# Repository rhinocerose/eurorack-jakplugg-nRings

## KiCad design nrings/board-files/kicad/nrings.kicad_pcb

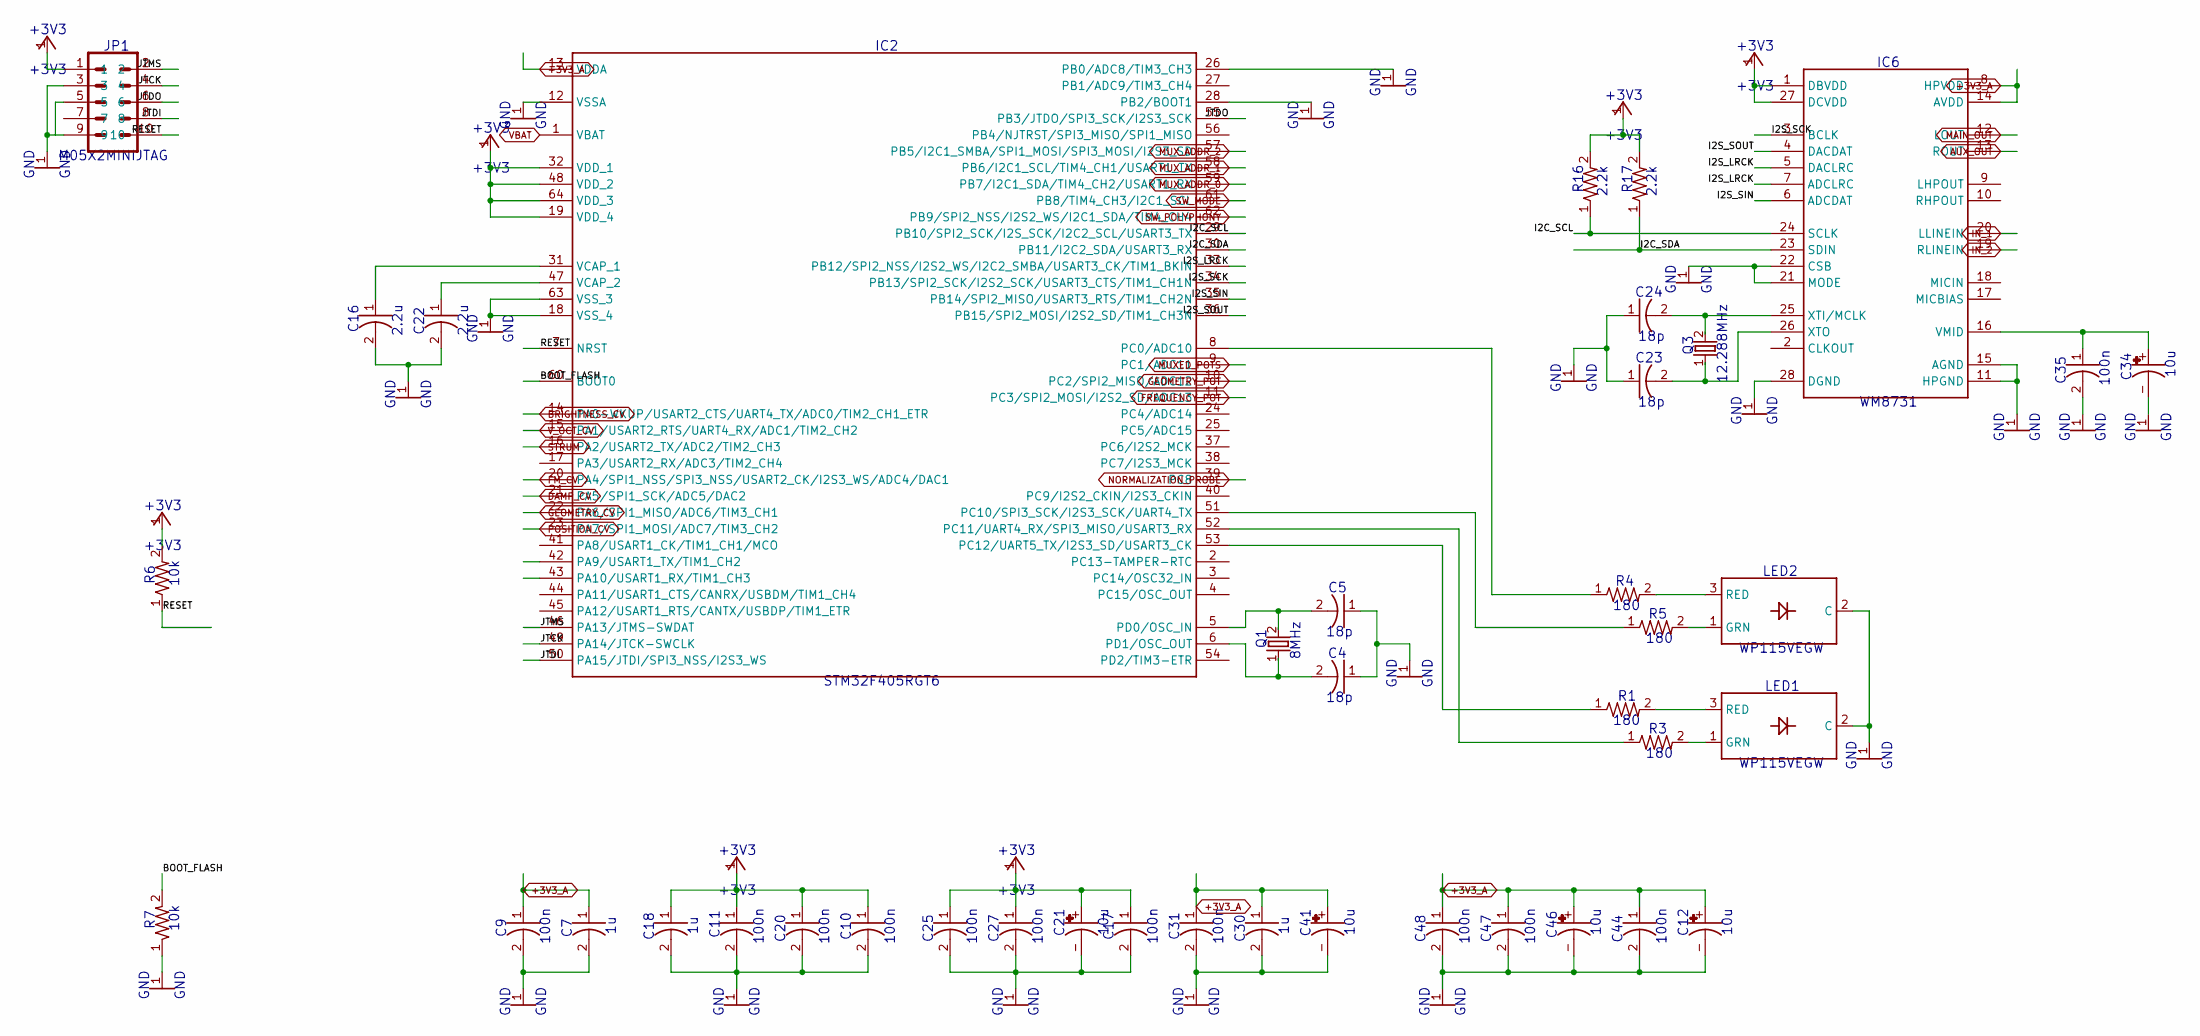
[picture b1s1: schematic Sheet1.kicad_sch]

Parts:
C4, C5, C23, C24: 18p; CAP_0603
C7, C18, C30: 1u; CAP_0603
C9, C10, C11, C17, C20, C25, C27, C31, C35, C44, C47, C48: 100n; CAP_0603
C12, C21, C34, C41, C46: 10u; PANASONIC_A
C16, C22: 2.2u; CAP_0805
IC2: STM32F405RGT6; TQFP-10X10-64
IC6: WM8731; SSOP28
JP1: M05X2MINIJTAG; 2X5-1.27
LED1, LED2: WP115VEGW; LED-BICOLOR-THROUGHHOLE
Q1: 8MHz; TSC_7A_CRYSTAL
Q3: 12.288MHz; TSC_7A_CRYSTAL
R1, R3, R4, R5: 180; RES_0603
R6, R7: 10k; RES_0603
R16, R17: 2.2k; RES_0603

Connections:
+3V3: C10.1, C11.1, C17.1, C18.1, C20.1, C21.+, C25.1, C27.1, IC2.19 (VDD_4), IC2.32 (VDD_1), IC2.48 (VDD_2), IC2.64 (VDD_3), IC6.1 (DBVDD), IC6.27 (DCVDD), JP1.1, R6.2, R16.2, R17.2; also elsewhere on the board
+3V3_A: C7.1, C9.1, C12.+, C30.1, C31.1, C41.+, C44.1, C46.+, C47.1, C48.1, IC2.13 (VDDA), IC6.8 (HPVDD), IC6.14 (AVDD); also elsewhere on the board
AUX_OUT: IC6.13 (ROUT); also elsewhere on the board
BOOT_FLASH: IC2.60 (BOOT0), R7.2
BRIGHTNESS_CV: IC2.14 (PA0-WKUP/USART2_CTS/UART4_TX/ADC0/TIM2_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); also elsewhere on the board
DAMP_CV: IC2.21 (PA5/SPI1_SCK/ADC5/DAC2); also elsewhere on the board
FM_CV: IC2.20 (PA4/SPI1_NSS/SPI3_NSS/USART2_CK/I2S3_WS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); also elsewhere on the board
FREQUENCY_POT: IC2.11 (PC3/SPI2_MOSI/I2S2_SD/ADC13); also elsewhere on the board
GEOMETRY_CV: IC2.22 (PA6/SPI1_MISO/ADC6/TIM3_CH1); also elsewhere on the board
GEOMETRY_POT: IC2.10 (PC2/SPI2_MISO/ADC12); also elsewhere on the board
GND: C4.1, C5.1, C7.2, C9.2, C10.2, C11.2, C12.-, C16.2, C17.2, C18.2, C20.2, C21.-, C22.2, C23.1, C24.1, C25.2, C27.2, C30.2, C31.2, C34.-, C35.2, C41.-, C44.2, C46.-, C47.2, C48.2, IC2.12 (VSSA), IC2.18 (VSS_4), IC2.26 (PB0/ADC8/TIM3_CH3), IC2.28 (PB2/BOOT1), IC2.63 (VSS_3), IC6.11 (HPGND), IC6.15 (AGND), IC6.21 (MODE), IC6.22 (CSB), IC6.28 (DGND), JP1.3, JP1.5, JP1.9, LED1.2 (C), LED2.2 (C), R7.1; also elsewhere on the board
I2C_SCL: IC2.29 (PB10/SPI2_SCK/I2S_SCK/I2C2_SCL/USART3_TX), IC6.24 (SCLK), R16.1
I2C_SDA: IC2.30 (PB11/I2C2_SDA/USART3_RX), IC6.23 (SDIN), R17.1
I2S_LRCK: IC2.33 (PB12/SPI2_NSS/I2S2_WS/I2C2_SMBA/USART3_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), IC6.5 (DACLRC), IC6.7 (ADCLRC)
I2S_SCK: IC2.34 (PB13/SPI2_SCK/I2S2_SCK/USART3_CTS/TIM1_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), IC6.3 (BCLK)
I2S_SIN: IC2.35 (PB14/SPI2_MISO/USART3_RTS/TIM1_CH2N), IC6.6 (ADCDAT)
I2S_SOUT: IC2.36 (PB15/SPI2_MOSI/I2S2_SD/TIM1_CH3N), IC6.4 (DACDAT)
IN_1: IC6.20 (LLINEIN); also elsewhere on the board
IN_2: IC6.19 (RLINEIN); also elsewhere on the board
JTCK: IC2.49 (PA14/JTCK-SWCLK), JP1.4
JTDI: IC2.50 (PA15/JTDI/SPI3_NSS/I2S3_WS), JP1.8
JTDO: IC2.55 (PB3/JTDO/SPI3_SCK/I2S3_SCK), JP1.6
JTMS: IC2.46 (PA13/JTMS-SWDAT), JP1.2
MAIN_OUT: IC6.12 (LOUT); also elsewhere on the board
MUXED_POTS: IC2.9 (PC1/ADC11); also elsewhere on the board
MUX_ADDR_0: IC2.59 (PB7/I2C1_SDA/TIM4_CH2/USART1_RX); also elsewhere on the board
MUX_ADDR_1: IC2.58 (PB6/I2C1_SCL/TIM4_CH1/USART1_TX); also elsewhere on the board
MUX_ADDR_2: IC2.57 (PB5/I2C1_SMBA/SPI1_MOSI/SPI3_MOSI/I2S3_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); also elsewhere on the board
unnamed: C5.2, IC2.5 (PD0/OSC_IN), Q1.2
unnamed: C4.2, IC2.6 (PD1/OSC_OUT), Q1.1
unnamed: LED1.3 (RED), R1.2
unnamed: C22.1, IC2.47 (VCAP_2)
unnamed: C34.+, C35.1, IC6.16 (VMID)
unnamed: C16.1, IC2.31 (VCAP_1)
unnamed: LED1.1 (GRN), R3.2
unnamed: LED2.3 (RED), R4.2
unnamed: LED2.1 (GRN), R5.2
unnamed: IC2.52 (PC11/UART4_RX/SPI3_MISO/USART3_RX), R3.1
unnamed: IC2.8 (PC0/ADC10), R4.1
unnamed: C24.2, IC6.25 (XTI/MCLK), Q3.2
unnamed: C23.2, IC6.26 (XTO), Q3.1
unnamed: IC2.53 (PC12/UART5_TX/I2S3_SD/USART3_CK), R1.1
unnamed: IC2.51 (PC10/SPI3_SCK/I2S3_SCK/UART4_TX), R5.1
NORMALIZATION_PROBE: IC2.39 (PC8); also elsewhere on the board
POSITION_CV: IC2.23 (PA7/SPI1_MOSI/ADC7/TIM3_CH2); also elsewhere on the board
RESET: IC2.7 (NRST), JP1.10, R6.1
STRUM: IC2.16 (PA2/USART2_TX/ADC2/TIM2_CH3); also elsewhere on the board
SW_MODE: IC2.61 (PB8/TIM4_CH3/I2C1_SCL); also elsewhere on the board
SW_POLYPHONY: IC2.62 (PB9/SPI2_NSS/I2S2_WS/I2C1_SDA/TIM4_CH4); also elsewhere on the board
V_OCT_CV: IC2.15 (PA1/USART2_RTS/UART4_RX/ADC1/TIM2_CH2); also elsewhere on the board

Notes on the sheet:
10u
C21
GND
180
C20
WM8731
C27
C16
C46
STM32F405RGT6
C18
C10
C31
C41
10k
WP115VEGW
C23
C22
LED2
+3V3
100n
8MHz
18p
IC2
M05X2MINIJTAG
JP1
2.2k
IC6
C48
R16
C11
R17
LED1
C12
C17
C47
C25
C44
C24
C30

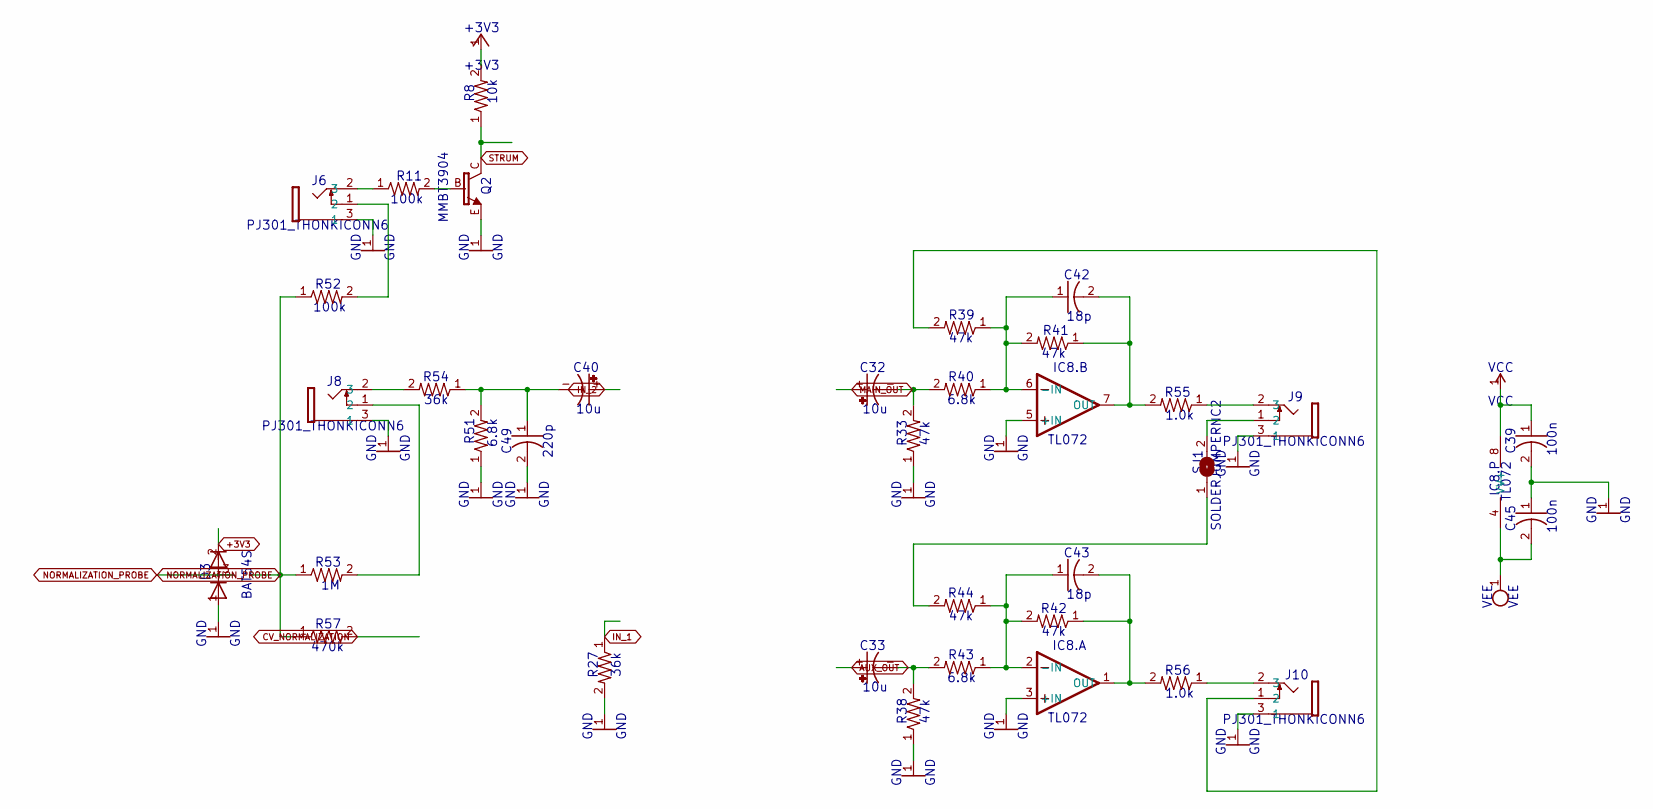
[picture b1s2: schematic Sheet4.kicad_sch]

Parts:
C32, C33, C40: 10u; PANASONIC_A
C39, C45: 100n; CAP_0603
C42, C43: 18p; CAP_0603
C49: 220p; CAP_0603
D3: BAT54S; SOT23
IC8: TL072; SO08
J6, J8, J9, J10: PJ301_THONKICONN6; THONKICONN
Q2: MMBT3904; SOT23-BEC
R8: 10k; RES_0603
R11, R52: 100k; RES_0603
R27, R54: 36k; RES_0603
R33, R38, R39, R41, R42, R44: 47k; RES_0603
R40, R43, R51: 6.8k; RES_0603
R53: 1M; RES_0603
R55, R56: 1.0k; RES_0603
R57: 470k; RES_0603
SJ1: SOLDERJUMPERNC2; SJ_2S-NOTRACE

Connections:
+3V3: D3.2 (C), R8.2; also elsewhere on the board
AUX_OUT: C33.+; also elsewhere on the board
CV_NORMALIZATION: R57.2; also elsewhere on the board
GND: C39.2, C45.1, C49.2, D3.1 (A), IC8.3 (+IN), IC8.5 (+IN), J6.3 (1), J8.3 (1), J9.3 (1), J10.3 (1), Q2.E, R27.2, R33.1, R38.1, R51.1; also elsewhere on the board
IN_1: R27.1; also elsewhere on the board
IN_2: C40.+; also elsewhere on the board
MAIN_OUT: C32.+; also elsewhere on the board
unnamed: J6.2 (3), R11.1
unnamed: C40.-, C49.1, R51.2, R54.1
unnamed: J6.1 (2), R52.2
unnamed: J8.2 (3), R54.2
unnamed: C33.-, R38.2, R43.2
unnamed: C43.1, IC8.2 (-IN), R42.2, R43.1, R44.1
unnamed: C43.2, IC8.1 (OUT), R42.1, R56.2
unnamed: J10.2 (3), R56.1
unnamed: C32.-, R33.2, R40.2
unnamed: C42.1, IC8.6 (-IN), R39.1, R40.1, R41.2
unnamed: C42.2, IC8.7 (OUT), R41.1, R55.2
unnamed: J9.2 (3), R55.1
unnamed: J8.1 (2), R53.2
unnamed: J10.1 (2), R39.2
unnamed: R44.2, SJ1.1
unnamed: J9.1 (2), SJ1.2
unnamed: Q2.B, R11.2
NORMALIZATION_PROBE: D3.3 (AC), R52.1, R53.1, R57.1; also elsewhere on the board
STRUM: Q2.C, R8.1; also elsewhere on the board
VCC: C39.1, IC8.8 (V+); also elsewhere on the board
VEE: C45.2, IC8.4 (V-); also elsewhere on the board

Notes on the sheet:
GND
1.0k
220p
6.8k
C49
R55
47k
10k
R56
R39
C42
100k
36k
R11
C40
SOLDERJUMPERNC2
R38
470k
SJ1
C33
PJ301_THONKICONN6
+3V3
R54
R40
10u
VEE
R57
R43
R51
R52
MMBT3904
J10
100n
C32
C43
R33
IC8.P
TL072
VCC
18p

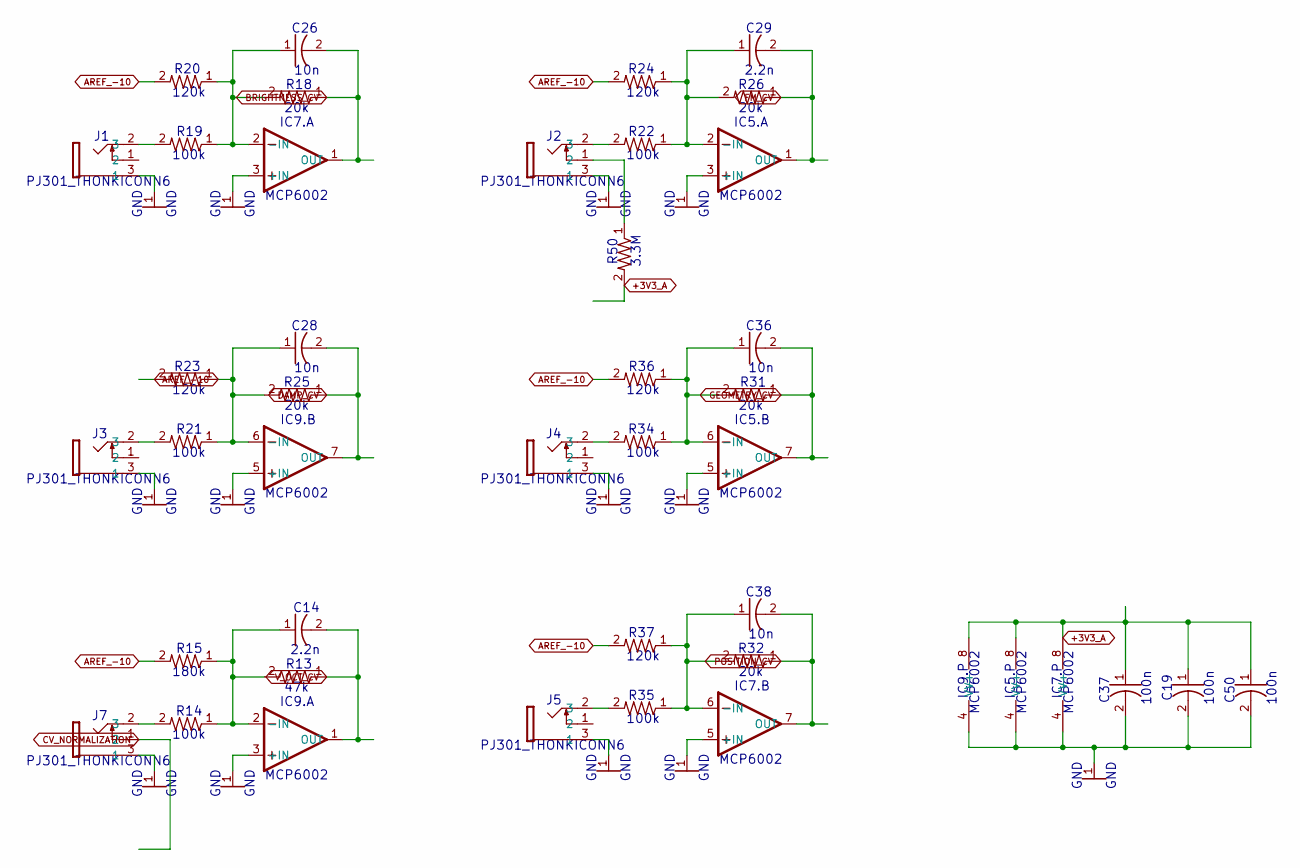
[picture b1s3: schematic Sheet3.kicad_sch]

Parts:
C14, C29: 2.2n; CAP_0603
C19, C37, C50: 100n; CAP_0603
C26, C28, C36, C38: 10n; CAP_0603
IC5, IC7, IC9: MCP6002; SO08
J1, J2, J3, J4, J5, J7: PJ301_THONKICONN6; THONKICONN
R13: 47k; RES_0603
R14, R19, R21, R22, R34, R35: 100k; RES_0603
R15: 180k; RES_0603
R18, R25, R26, R31, R32: 20k; RES_0603
R20, R23, R24, R36, R37: 120k; RES_0603
R50: 3.3M; RES_0603

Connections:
+3V3_A: C19.1, C37.1, C50.1, IC5.8 (V+), IC7.8 (V+), IC9.8 (V+), R50.2; also elsewhere on the board
AREF_-10: R15.2, R20.2, R23.2, R24.2, R36.2, R37.2; also elsewhere on the board
BRIGHTNESS_CV: C26.2, IC7.1 (OUT), R18.1; also elsewhere on the board
CV_NORMALIZATION: J7.1 (2); also elsewhere on the board
DAMP_CV: C28.2, IC9.7 (OUT), R25.1; also elsewhere on the board
FM_CV: C29.2, IC5.1 (OUT), R26.1; also elsewhere on the board
GEOMETRY_CV: C36.2, IC5.7 (OUT), R31.1; also elsewhere on the board
GND: C19.2, C37.2, C50.2, IC5.3 (+IN), IC5.4 (V-), IC5.5 (+IN), IC7.3 (+IN), IC7.4 (V-), IC7.5 (+IN), IC9.3 (+IN), IC9.4 (V-), IC9.5 (+IN), J1.3 (1), J2.3 (1), J3.3 (1), J4.3 (1), J5.3 (1), J7.3 (1); also elsewhere on the board
unnamed: J1.2 (3), R19.2
unnamed: C26.1, IC7.2 (-IN), R18.2, R19.1, R20.1
unnamed: J7.2 (3), R14.2
unnamed: J2.2 (3), R22.2
unnamed: C29.1, IC5.2 (-IN), R22.1, R24.1, R26.2
unnamed: J4.2 (3), R34.2
unnamed: J3.2 (3), R21.2
unnamed: C28.1, IC9.6 (-IN), R21.1, R23.1, R25.2
unnamed: C14.1, IC9.2 (-IN), R13.2, R14.1, R15.1
unnamed: C36.1, IC5.6 (-IN), R31.2, R34.1, R36.1
unnamed: J5.2 (3), R35.2
unnamed: C38.1, IC7.6 (-IN), R32.2, R35.1, R37.1
unnamed: J2.1 (2), R50.1
POSITION_CV: C38.2, IC7.7 (OUT), R32.1; also elsewhere on the board
V_OCT_CV: C14.2, IC9.1 (OUT), R13.1; also elsewhere on the board

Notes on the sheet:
R31
10n
20k
MCP6002
IC9.B
GND
PJ301_THONKICONN6
2.2n
C50
R20
IC7.P
100k
C26
C29
3.3M
R50
C28
R24
100n
47k
C19
120k
IC7.B
IC5.P
R18
R14
C14
R25
R26
R19
C37
R15
IC9.A
IC5.A
R37
R21
IC9.P
R22
R35
R32

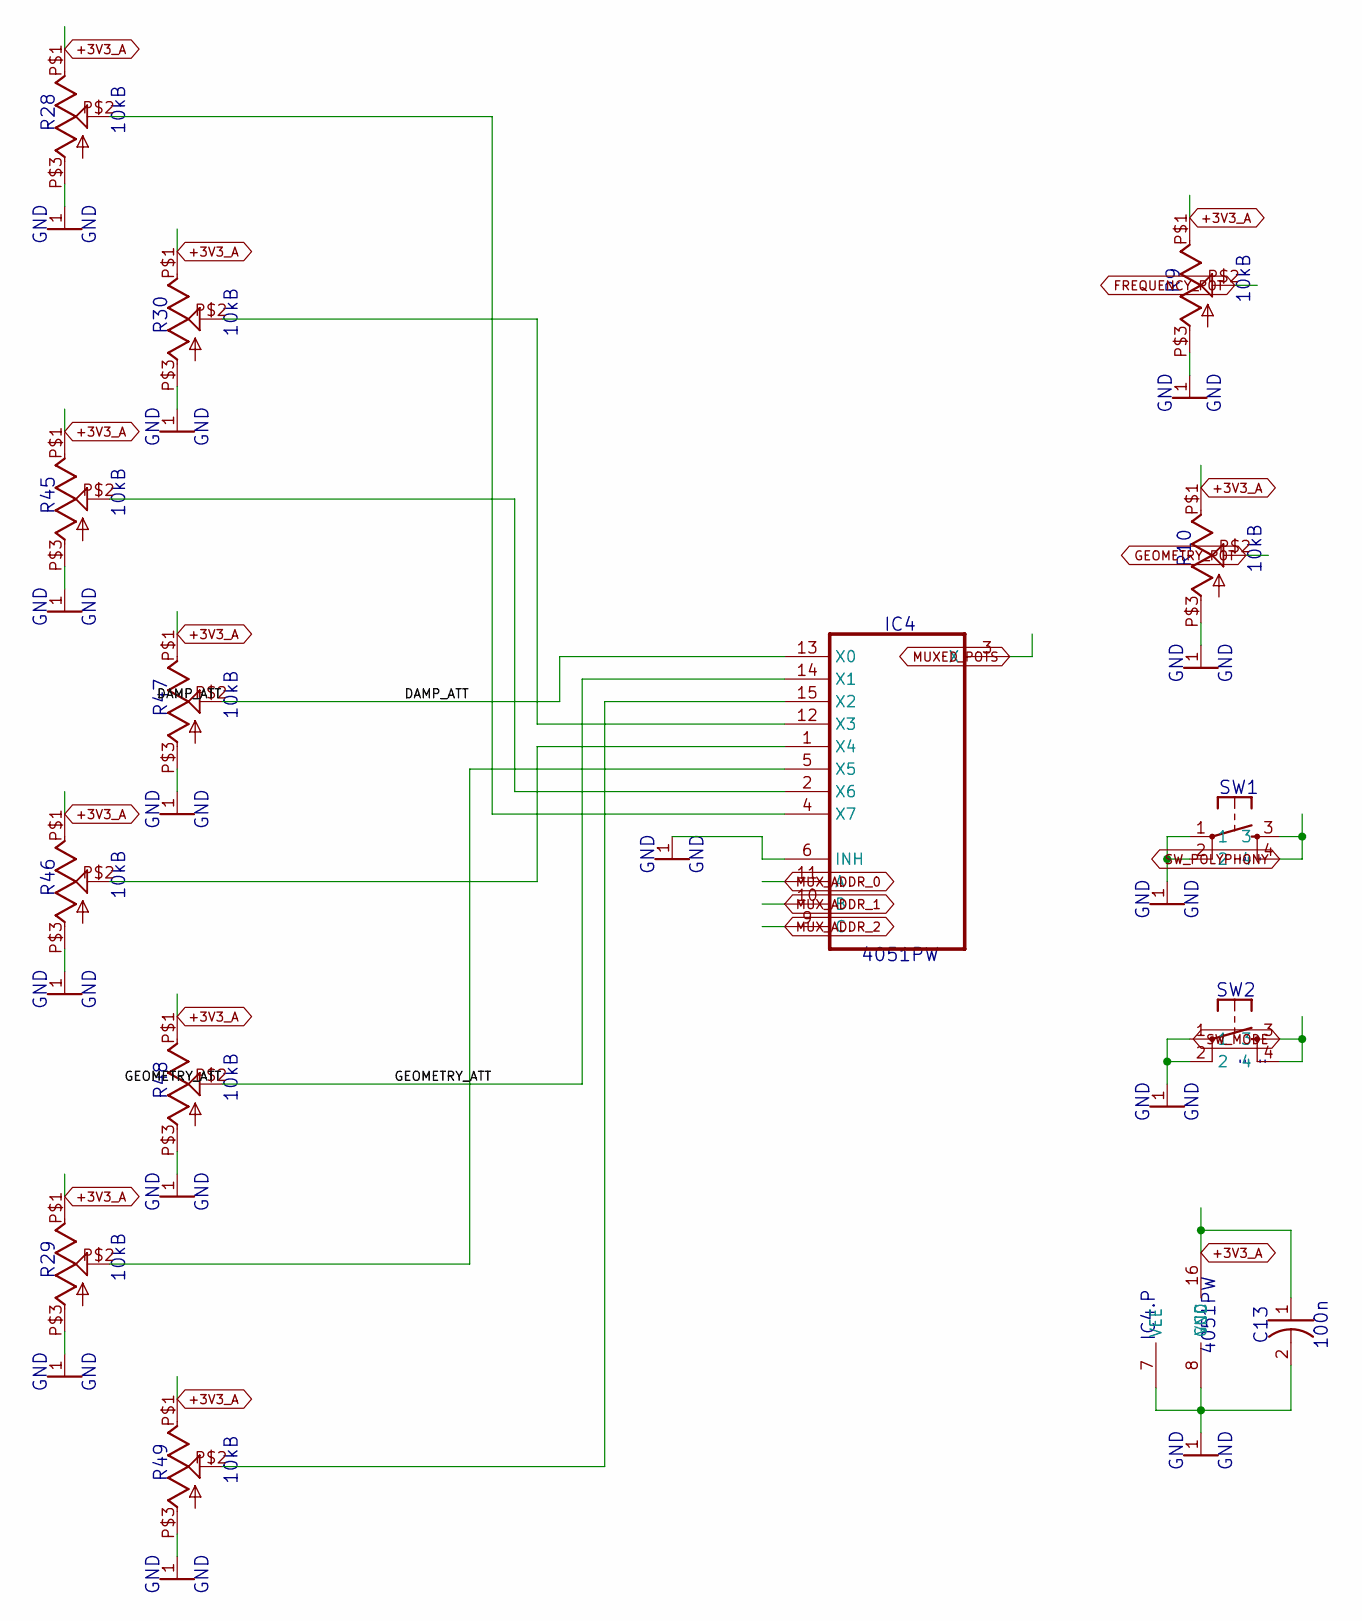
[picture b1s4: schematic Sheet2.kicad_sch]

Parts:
C13: 100n; CAP_0603
IC4: 4051PW; TSSOP16
R9, R10, R28, R29, R30: 10kB; ALPS_POT_VERTICAL_PS
R45, R46, R47, R48, R49: 10kB; ALPS_POT_VERTICAL
SW1, SW2: TAC_SWITCHPTH; TACTILE-PTH

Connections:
+3V3_A: C13.1, IC4.16 (VCC), R9.P$1 (E), R10.P$1 (E), R28.P$1 (E), R29.P$1 (E), R30.P$1 (E), R45.P$1 (E), R46.P$1 (E), R47.P$1 (E), R48.P$1 (E), R49.P$1 (E); also elsewhere on the board
BRIGHTNESS_ATT: IC4.2 (X6), R45.P$2 (S)
BRIGHTNESS_POT: IC4.4 (X7), R28.P$2 (S)
DAMP_ATT: IC4.13 (X0), R47.P$2 (S)
DAMP_POT: IC4.5 (X5), R29.P$2 (S)
FREQUENCY_ATT: IC4.1 (X4), R46.P$2 (S)
FREQUENCY_POT: R9.P$2 (S); also elsewhere on the board
GEOMETRY_ATT: IC4.14 (X1), R48.P$2 (S)
GEOMETRY_POT: R10.P$2 (S); also elsewhere on the board
GND: C13.2, IC4.6 (INH), IC4.7 (VEE), IC4.8 (GND), R9.P$3 (A), R9.P$4, R9.P$5, R10.P$3 (A), R10.P$4, R10.P$5, R28.P$3 (A), R28.P$4, R28.P$5, R29.P$3 (A), R29.P$4, R29.P$5, R30.P$3 (A), R30.P$4, R30.P$5, R45.P$3 (A), R45.P$4, R45.P$5, R46.P$3 (A), R46.P$4, R46.P$5, R47.P$3 (A), R47.P$4, R47.P$5, R48.P$3 (A), R48.P$4, R48.P$5, R49.P$3 (A), R49.P$4, R49.P$5, SW1.1, SW1.2, SW2.1, SW2.2; also elsewhere on the board
MUXED_POTS: IC4.3 (X); also elsewhere on the board
MUX_ADDR_0: IC4.11 (A); also elsewhere on the board
MUX_ADDR_1: IC4.10 (B); also elsewhere on the board
MUX_ADDR_2: IC4.9 (C); also elsewhere on the board
POSITION_ATT: IC4.15 (X2), R49.P$2 (S)
POSITION_POT: IC4.12 (X3), R30.P$2 (S)
SW_MODE: SW2.3, SW2.4; also elsewhere on the board
SW_POLYPHONY: SW1.3, SW1.4; also elsewhere on the board

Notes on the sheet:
10kB
GND
R28
R48
R49
C13
R45
" "
R47
100n
R46
4051PW
SW1
R29
IC4
IC4.P
R30
R10
SW2

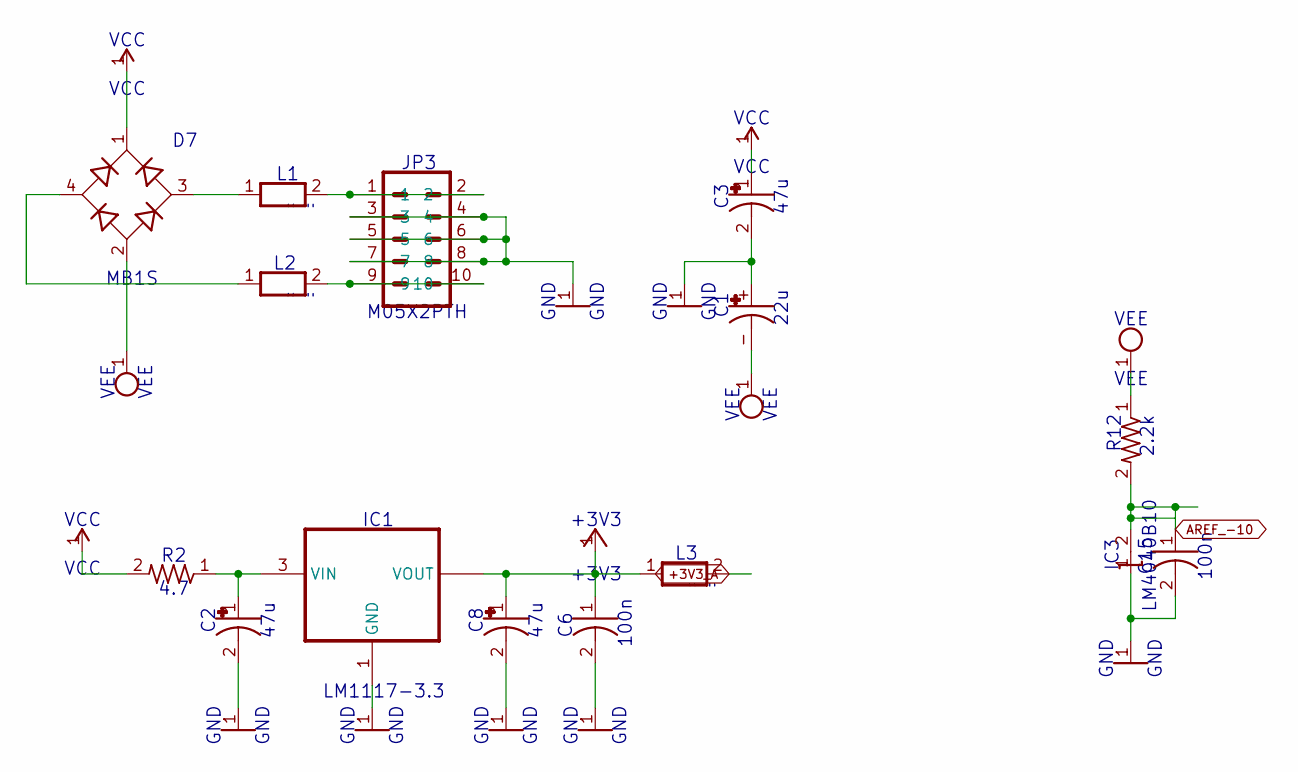
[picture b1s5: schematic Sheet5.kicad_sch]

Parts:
C1: 22u; PANASONIC_C
C2, C3, C8: 47u; CAPAE-5.3X5.3H7
C6, C15: 100n; CAP_0603
D7: MB1S; SOP-4_6.5X2.54
IC1: LM1117-3.3; SOT223-4
IC3: LM4040B10; DBZ_R-PDSO-G3
JP3: M05X2PTH; AVR_ICSP
L1, L2, L3: WE-CBF_0603; 0603
R2: 4.7; R1206
R12: 2.2k; RES_0603

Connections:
+3V3: C6.1, C8.1 (+), IC1.2 (VOUT), IC1.4 (VOUT), L3.1; also elsewhere on the board
+3V3_A: L3.2; also elsewhere on the board
AREF_-10: C15.1, IC3.2 (A), R12.2; also elsewhere on the board
GND: C1.+, C2.2 (-), C3.2 (-), C6.2, C8.2 (-), C15.2, IC1.1 (GND), IC3.1 (C), JP3.3, JP3.4, JP3.5, JP3.6, JP3.7, JP3.8; also elsewhere on the board
unnamed: C2.1 (+), IC1.3 (VIN), R2.1
unnamed: JP3.1, JP3.2, L1.2
unnamed: JP3.9, JP3.10, L2.2
Net_95: D7.3 (AC2), L1.1
Net_96: D7.4 (AC1), L2.1
VCC: C3.1 (+), D7.1 (+), R2.2; also elsewhere on the board
VEE: C1.-, D7.2 (-), R12.1; also elsewhere on the board

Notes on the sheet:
GND
LM4040B10
47u
+3V3
" "
VEE
100n
R12
C15
MB1S
VCC
2.2k
JP3
IC3
22u
IC1
LM1117-3.3
M05X2PTH
4.7

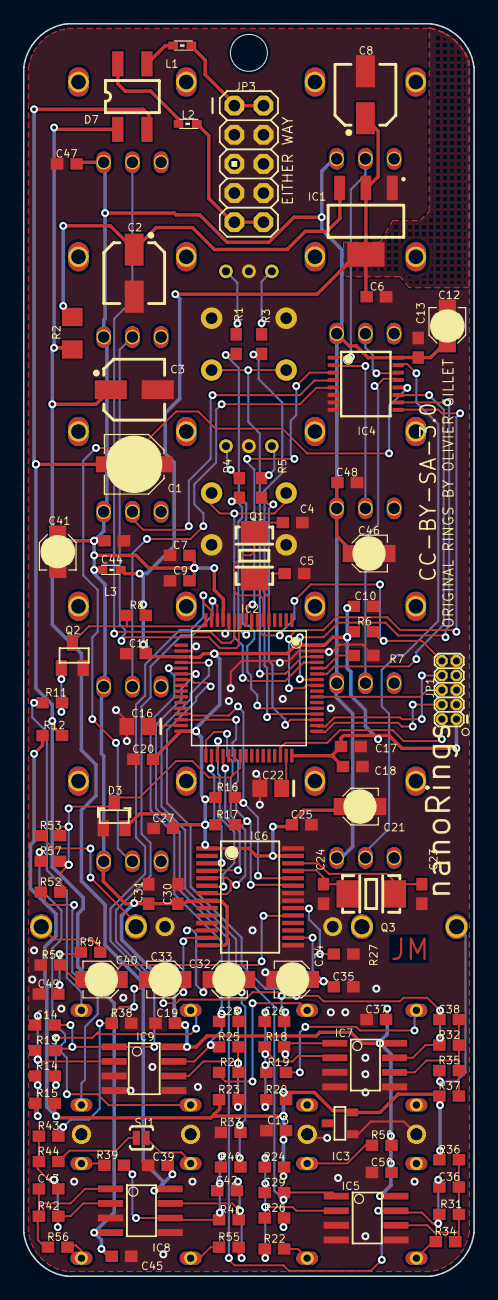
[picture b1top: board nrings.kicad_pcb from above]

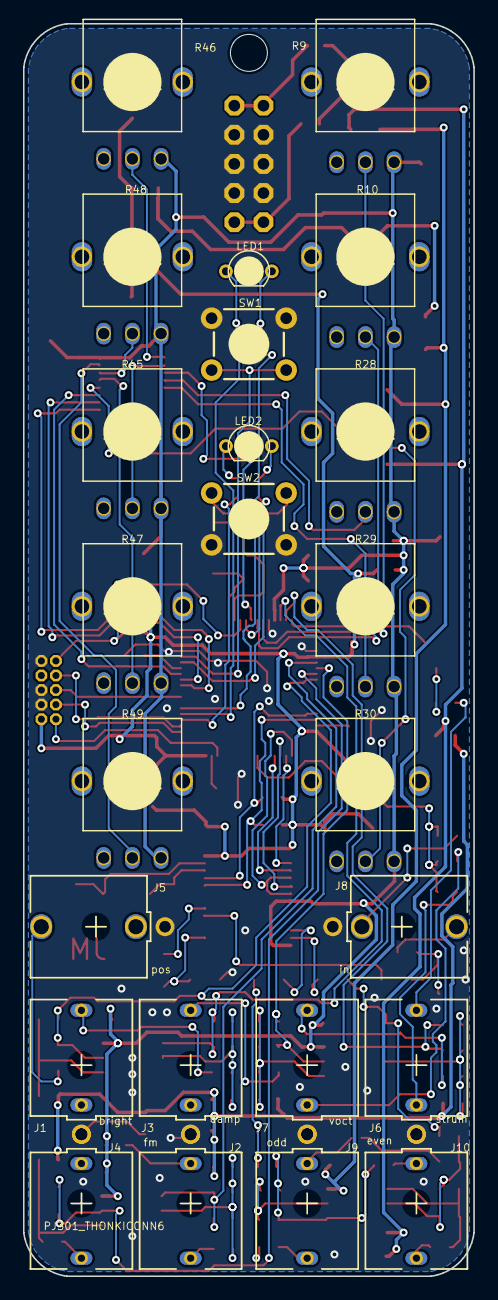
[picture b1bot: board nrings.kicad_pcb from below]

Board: 2 copper layers, 39.3 x 109.2 mm, 142 parts (24 on the bottom side), 97 nets.

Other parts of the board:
@HOLE0: (no value)

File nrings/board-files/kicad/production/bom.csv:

Designator,Footprint,Quantity,Value,LCSC Part #
@HOLE0,,1,,
C1,PANASONIC_C,1,22u,
"C10, C25, C31, C35, C48, C6",CAP_0603_C6,6,100n,
"C11, C15, C19, C20, C27, C37, C47, C50, C9",CAP_0603_C7,9,100n,
C12,PANASONIC_A,1,10u,
"C13, C17",CAP_0603_C13,2,100n,
"C14, C29",CAP_0603_C6,2,2.2n,
"C16, C22",CAP_0805,2,2.2u,
C18,CAP_0603_C13,1,1u,
C2,CAPAE-5.3x5.3h7,1,47u,
C21,PANASONIC_A_C21,1,10u,
C23,CAP_0603_C23,1,18p,
C24,CAP_0603_C24,1,18p,
C26,CAP_0603_C6,1,10n,
"C28, C36, C38",CAP_0603_C7,3,10n,
C3,CAPAE-5.3x5.3h7_C3,1,47u,
C30,CAP_0603_C6,1,1u,
C32,PANASONIC_A_C32,1,10u,
C33,PANASONIC_A_C33,1,10u,
C34,PANASONIC_A_C34,1,10u,
C39,CAP_0603_C39,1,100n,
"C4, C5",CAP_0603,2,18p,
C40,PANASONIC_A_C40,1,10u,
C41,PANASONIC_A_C41,1,10u,
C42,CAP_0603_C6,1,18p,
C43,CAP_0603_C7,1,18p,
C44,CAP_0603_C44,1,100n,
C45,CAP_0603_C45,1,100n,
C46,PANASONIC_A_C46,1,10u,
C49,CAP_0603_C7,1,220p,
C7,CAP_0603_C7,1,1u,
C8,CAPAE-5.3x5.3h7_C8,1,47u,
D3,SOT23,1,BAT54S,
D7,SOP-4_6.5x2.54,1,MB1S,
IC1,SOT223-4,1,LM1117-3.3,
IC2,TQFP-10X10-64,1,STM32F405RGT6,
IC3,DBZ_R-PDSO-G3,1,LM4040B10,
IC4,TSSOP16,1,4051PW,
IC5,SO08,1,MCP6002,
IC6,SSOP28,1,WM8731,
IC7,SO08_IC7,1,MCP6002,
IC8,SO08_IC8,1,TL072,
IC9,SO08_IC9,1,MCP6002,
"J1, J3, J6, J7",Thonkiconn,4,PJ301_THONKICONN6,
"J10, J2",Thonkiconn_J2,2,PJ301_THONKICONN6,
J4,Thonkiconn_J4,1,PJ301_THONKICONN6,
"J5, J8",Thonkiconn_J5,2,PJ301_THONKICONN6,
J9,Thonkiconn_J9,1,PJ301_THONKICONN6,
JP1,2X5-1.27,1,M05X2MINIJTAG,
JP3,AVR_ICSP,1,M05X2PTH,
L1,0603,1,WE-CBF_0603,
L2,0603_L2,1,WE-CBF_0603,
L3,0603_L3,1,WE-CBF_0603,
"LED1, LED2",LED-BICOLOR-THROUGHHOLE,2,WP115VEGW,
Q1,TSC_7A_crystal,1,8MHz,
Q2,SOT23-BEC,1,MMBT3904,
Q3,TSC_7A_crystal_Q3,1,12.288MHz,
"R1, R3",RES_0603,2,180,
"R10, R28, R29, R30",ALPS_POT_VERTICAL_PS_R10,4,10kB,
"R11, R14, R19, R22",RES_0603_R8,4,100k,
"R12, R16, R17",RES_0603_R6,3,2.2k,
"R13, R38, R41",RES_0603_R6,3,47k,
R15,RES_0603_R8,1,180k,
"R18, R26",RES_0603_R6,2,20k,
R2,R1206,1,4.7,
"R20, R24",RES_0603_R8,2,120k,
"R21, R34, R35, R52",RES_0603_R6,4,100k,
"R23, R36, R37",RES_0603_R6,3,120k,
"R25, R31, R32",RES_0603_R8,3,20k,
R27,RES_0603_R27,1,36k,
"R33, R42, R44",RES_0603_R8,3,47k,
R39,RES_0603_R39,1,47k,
R4,RES_0603_R4,1,180,
"R40, R43, R51",RES_0603_R8,3,6.8k,
"R45, R47, R48, R49",ALPS_POT_VERTICAL,4,10kB,
R46,ALPS_POT_VERTICAL_R46,1,10kB,
R5,RES_0603_R5,1,180,
R50,RES_0603_R8,1,3.3M,
R53,RES_0603_R6,1,1M,
R54,RES_0603_R8,1,36k,
R55,RES_0603_R8,1,1.0k,
R56,RES_0603_R6,1,1.0k,
R57,RES_0603_R6,1,470k,
R6,RES_0603_R6,1,10k,
R7,RES_0603_R7,1,10k,
R8,RES_0603_R8,1,10k,
R9,ALPS_POT_VERTICAL_PS,1,10kB,
SJ1,SJ_2S-NOTRACE,1,SOLDERJUMPERNC2,
SW1,TACTILE-PTH,1,TAC_SWITCHPTH,
SW2,TACTILE-PTH_SW2,1,TAC_SWITCHPTH,

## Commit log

2025-08-07 converted to eagle
2025-08-07 Kicad

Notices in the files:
nrings/board-files/kicad/nrings.kicad_pcb:
CC-BY-SA-3.0
